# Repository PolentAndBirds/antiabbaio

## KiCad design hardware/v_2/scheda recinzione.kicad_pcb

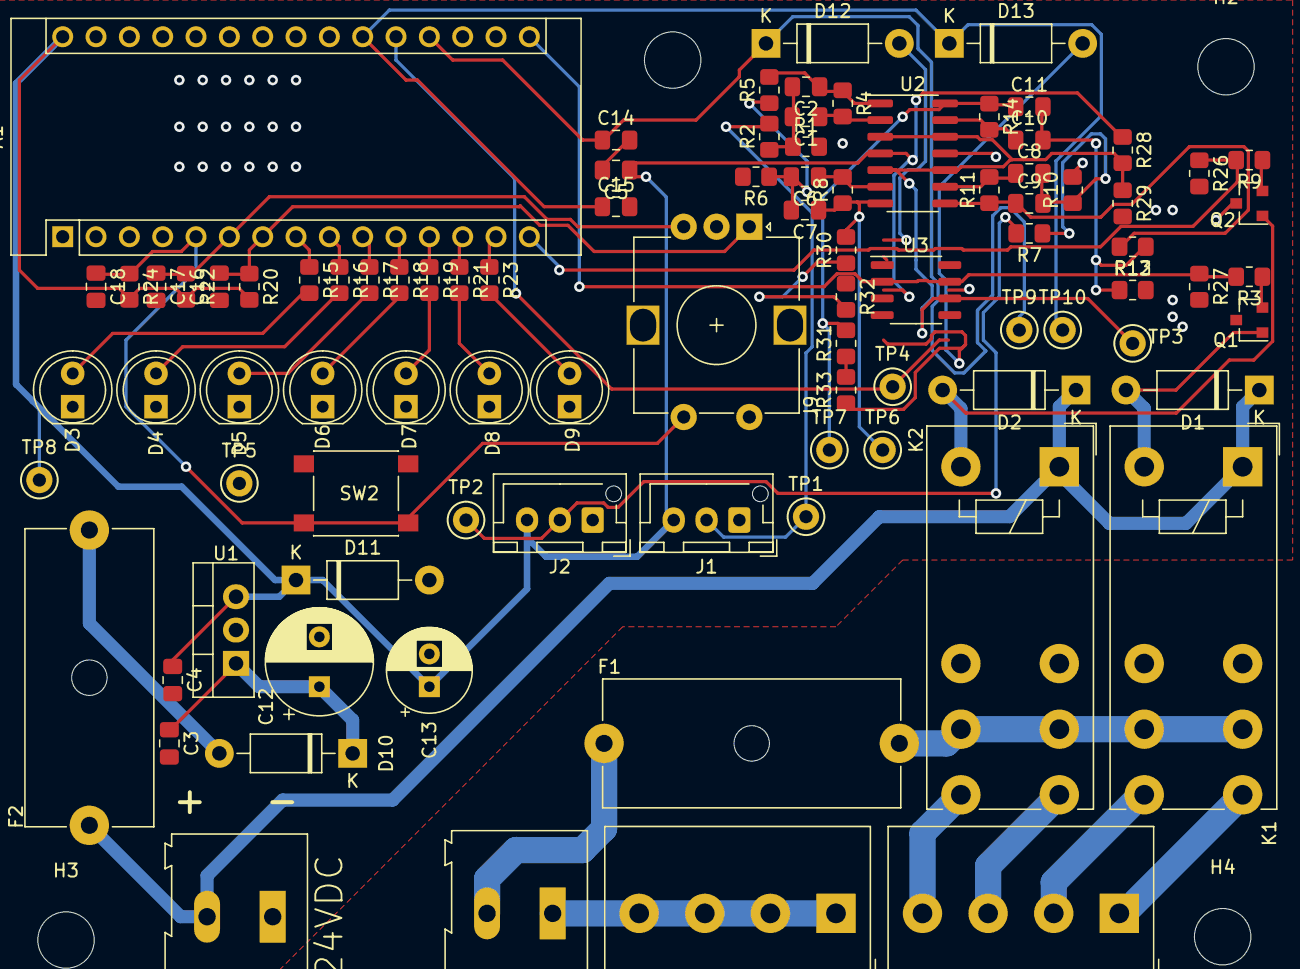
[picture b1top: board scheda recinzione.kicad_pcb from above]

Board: 2 copper layers, 95 parts (0 on the bottom side), 57 nets.

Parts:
A1: Arduino_Nano_v3.x; Arduino_Nano
C1, C2, C6, C7, C8, C9, C10, C11: 100nF; C_0805_2012Metric_Pad1.18x1.45mm_HandSolder
C3, C4, C16, C17, C18: 10n; C_0805_2012Metric_Pad1.18x1.45mm_HandSolder
C5: C; C_0805_2012Metric_Pad1.18x1.45mm_HandSolder
C12: 100uF 35V; CP_Radial_D8.0mm_P3.80mm
C13: 10uF 10V; CP_Radial_D6.3mm_P2.50mm
C14, C15: 220p; C_0805_2012Metric_Pad1.18x1.45mm_HandSolder
D1, D2, D10, D12, D13: 1N4007; D_DO-41_SOD81_P10.16mm_Horizontal
D3, D4, D5, D6, D7, D8, D9: LED; LED_D5.0mm
D11: 1N4734; D_DO-41_SOD81_P10.16mm_Horizontal
F1, F2: Fuse; Fuseholder_Cylinder-5x20mm_Schurter_0031_8201_Horizontal_Op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
H1, H2, H3, H4: MountingHole; MountingHole_4.3mm_M4
J1, J2: Conn_01x03; JST_XH_B3B-XH-AM_1x03_P2.50mm_Vertical
J3, J7: Screw_Terminal_01x02; TerminalBlock_Altech_AK300-2_P5.00mm
J4, J5: Screw_Terminal_01x04; Altech_AK300_1x04_P5.00mm_45-Degree
J9: Conn_01x03; RotaryEncoder_Alps_EC12E-Switch_Vertical_H20mm
K1, K2: FINDER-40.52; Relay_DPDT_Finder_40.52
Q1, Q2: BC337; SOT-23
R1, R10: 150R; R_0805_2012Metric_Pad1.20x1.40mm_HandSolder
R2, R5, R7, R12: 12k; R_0805_2012Metric_Pad1.20x1.40mm_HandSolder
R3, R9, R30: 1k; R_0805_2012Metric_Pad1.20x1.40mm_HandSolder
R4, R11: 33k; R_0805_2012Metric_Pad1.20x1.40mm_HandSolder
R6, R13: 120R; R_0805_2012Metric_Pad1.20x1.40mm_HandSolder
R8, R14: 27k; R_0805_2012Metric_Pad1.20x1.40mm_HandSolder
R15, R16, R17, R18, R19, R21, R23: 330R; R_0805_2012Metric_Pad1.20x1.40mm_HandSolder
R20, R22, R24, R26, R27, R29: 10k; R_0805_2012Metric_Pad1.20x1.40mm_HandSolder
R28: 8k2; R_0805_2012Metric_Pad1.20x1.40mm_HandSolder
R31: 1K; R_0805_2012Metric_Pad1.20x1.40mm_HandSolder
R32, R33: 2k2; R_0805_2012Metric_Pad1.20x1.40mm_HandSolder
SW2: SW_Push; SW_Push_1P1T_NO_6x6mm_H9.5mm
TP1, TP2, TP3, TP4, TP5, TP6, TP7, TP8, TP9, TP10: TestPoint; TestPoint_Keystone_5000-5004_Miniature
U1: LM7805_TO220; TO-220-3_Vertical
U2: TL084; SO-14_3.9x8.65mm_P1.27mm
U3: TL082; SO-8_3.9x4.9mm_P1.27mm

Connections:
+5V: A1.30, C4.1, C5.1, C13.1, D11.1, J1.3, J2.3, R20.2, R22.2, R24.2, R28.1, TP8.1, U1.3, U2.4, U3.8
+24V: D1.1, D2.1, F2.2, J7.2, K1.A1, K2.A1
GND: A1.4, A1.29, C3.2, C4.2, C5.2, C12.2, C13.2, C14.2, C15.2, C16.1, C17.2, C18.2, D3.1, D4.1, D5.1, D6.1, D7.1, D8.1, D9.1, D11.2, J1.1, J2.1, J7.1, J9.C, J9.S1, Q1.3, Q2.3, R1.2, R6.2, R10.2, R13.2, R26.2, R27.2, R29.2, SW2.2, TP5.1, U1.2, U2.11, U3.4
unnamed: A1.5, C18.1, J9.S2, R24.1, SW2.1
unnamed: A1.6, C17.1, J9.B, R22.1
unnamed: A1.7, C16.2, J9.A, R20.1
unnamed: A1.8, R15.1
unnamed: A1.9, R16.1
unnamed: A1.10, R17.1
unnamed: A1.11, R18.1
unnamed: A1.12, R19.1
unnamed: A1.13, R21.1
unnamed: A1.14, R23.1
unnamed: A1.15, R9.2, R26.1
unnamed: A1.16, R3.2, R27.1
unnamed: A1.19, C14.1, D12.1, TP9.1
unnamed: A1.20, TP4.1
unnamed: A1.21, C15.1, D13.1, TP10.1
unnamed: C1.1, R4.2, U2.2
unnamed: C1.2, C2.2, R1.1, R2.1
unnamed: C2.1, R4.1, R5.2, U2.1
unnamed: C6.1, R8.2, U2.6
unnamed: C6.2, C7.2, R5.1, R6.1
unnamed: C7.1, R8.1, R30.2, TP6.1, U2.7
unnamed: C8.1, R11.2, U2.9
unnamed: C8.2, C9.2, R7.1, R10.1
unnamed: C9.1, R11.1, R12.2, U2.8
unnamed: C10.1, R14.2, U2.13
unnamed: C10.2, C11.2, R12.1, R13.1
unnamed: C11.1, R14.1, R31.2, TP7.1, U2.14
unnamed: C3.1, C12.1, D10.1, U1.1
unnamed: D1.2, K1.A2, Q1.1
unnamed: D2.2, K2.A2, Q2.1
unnamed: D3.2, R15.2
unnamed: D4.2, R16.2
unnamed: D5.2, R17.2
unnamed: D6.2, R18.2
unnamed: D7.2, R19.2
unnamed: D8.2, R21.2
unnamed: D9.2, R23.2
unnamed: D10.2, F2.1
unnamed: D12.2, R32.1, U3.1
unnamed: D13.2, R33.1, U3.7
unnamed: F1.1, K1.11, K1.21, K2.11, K2.21
unnamed: F1.2, J3.2
unnamed: J1.2, R2.2, TP1.1
unnamed: J2.2, R7.2, TP2.1
unnamed: J3.1, J4.1, J4.2, J4.3, J4.4
unnamed: J5.1, K1.14
unnamed: J5.2, K1.24
unnamed: J5.3, K2.14
unnamed: J5.4, K2.24
unnamed: Q1.2, R3.1
unnamed: Q2.2, R9.1
unnamed: R30.1, R32.2, U3.2
unnamed: R31.1, R33.2, U3.6
VCC: R28.2, R29.1, TP3.1, U2.3, U2.5, U2.10, U2.12, U3.3, U3.5

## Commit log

2022-06-13 prima versione
2022-06-18 nuove cartelle
2022-06-20 v2 da finire
